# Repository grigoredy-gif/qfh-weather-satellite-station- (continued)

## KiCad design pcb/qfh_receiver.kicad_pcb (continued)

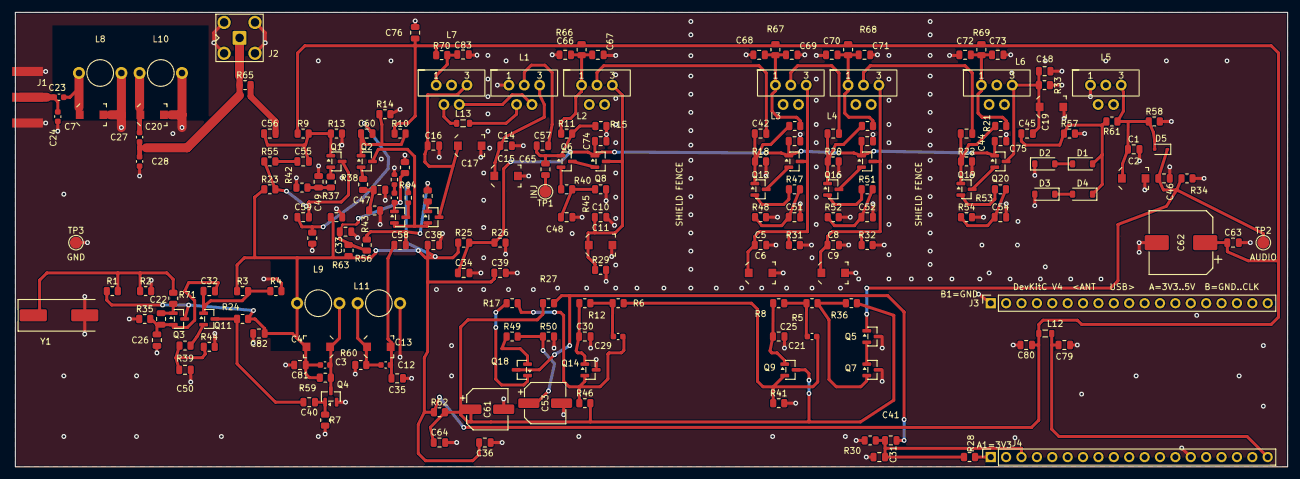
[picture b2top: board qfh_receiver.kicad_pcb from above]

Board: 2 copper layers, 210.0 x 75.0 mm, 205 parts (0 on the bottom side), 90 nets.

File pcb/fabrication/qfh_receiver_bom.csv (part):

"Refs","Value","Spec","Footprint","MPN","Farnell","Qty","DNP"
"C1,C5,C8,C10,C14,C16,C18,C35,C46","47p","NP0/C0G ceramic 0805, 50 V","Capacitor_SMD:C_0805_2012Metric","","","9",""
"C2,C6,C9,C11,C15,C17,C19","5.8-20p","SEHWA STC3MD20-T1 SMD trimmer 5.8-20 pF, N1300 (LCSC C22468122); pad 2 = rotor (cold side)","qfh_receiver:C_Trimmer_JZ_STC3","STC3MD20-T1","","7",""
"C3","4.7p","NP0/C0G 0603, 50 V, +/-0.25 pF (FH 0603CG4R7C500NT, LCSC C1669); fixed part of the x5 tank, with the 2-6 pF trimmer C4","Capacitor_SMD:C_0603_1608Metric","","","1",""
"C4","2-6p","SEHWA STC3MA06-T1 SMD trimmer 2-6 pF, Q 500 (LCSC C22468120); pad 2 = rotor (cold side, vcc)","qfh_receiver:C_Trimmer_JZ_STC3","STC3MA06-T1","","1",""
"C7,C13,C20","2-6p","SEHWA STC3MA06-T1 SMD trimmer 2-6 pF, Q 500 (LCSC C22468120); pad 2 = rotor (cold side)","qfh_receiver:C_Trimmer_JZ_STC3","STC3MA06-T1","","3",""
"C12","6.8p","NP0/C0G 0603, 50 V (FH 0603CG6R8C500NT, LCSC C1679); fixed part of the LO top arm, with the 2-6 pF trimmer C13","Capacitor_SMD:C_0603_1608Metric","","","1",""
"C21","2.7n","X7R 0603, 50 V, 10 % (FH 0603B272K500NT, LCSC C1609)","Capacitor_SMD:C_0603_1608Metric","","","1",""
"C22","22p","NP0/C0G 0805, 50 V; Colpitts C1 for a CL 20 pF crystal (22p in series with 180p + strays = about 20 pF)","Capacitor_SMD:C_0805_2012Metric","","","1",""
"C23,C27","10p","NP0/C0G 0603, 50 V, 5 % (Samsung CL10C100JB8NNNC, LCSC C1634); BPF tap, 10p/68p keeps the 0.128 ratio","Capacitor_SMD:C_0603_1608Metric","","","2",""
"C24,C28","68p","NP0/C0G 0603, 50 V, 5 % (Samsung CL10C680JB8NNNC, LCSC C28262); BPF tap","Capacitor_SMD:C_0603_1608Metric","","","2",""
"C25,C31","2.2n","C0G 0805, 50 V, 5 % (Samsung CL21C222JBFNNNE, LCSC C28260)","Capacitor_SMD:C_0805_2012Metric","","","2",""
"C26","180p","NP0/C0G ceramic 0805, 50 V","Capacitor_SMD:C_0805_2012Metric","","","1",""
"C29","8.2n","X7R 0603, 50 V, 10 % (FH 0603B822K500NT, LCSC C1322360)","Capacitor_SMD:C_0603_1608Metric","","","1",""
"C30","1n","X7R 0805, 50 V (Samsung CL21B102KBCNNNC, LCSC C46653); 1.2n -> 1.0n in the cost-down, audio corner 6.1 -> 6.6 kHz","Capacitor_SMD:C_0805_2012Metric","","","1",""
"C32,C33,C47","10n","X7R ceramic 0805, 50 V","Capacitor_SMD:C_0805_2012Metric","","","3",""
"C34,C36-C39,C48-C52,C54,C63,C64,C66-C82","100n","X7R ceramic 0805, 50 V","Capacitor_SMD:C_0805_2012Metric","","","30",""
"C40,C42-C45,C55-C60,C65","1n","X7R ceramic 0805, 50 V","Capacitor_SMD:C_0805_2012Metric","","","12",""
"C41","1u","X7R ceramic 0805, 16 V or more","Capacitor_SMD:C_0805_2012Metric","","","1",""
"C53,C61","100u","SMD aluminium electrolytic 16 V, 6.3x7.7 mm","Capacitor_SMD:CP_Elec_6.3x7.7","","","2",""
"C62","1000u","SMD aluminium electrolytic 1000 uF 10 V, 90 mOhm, D10 x 10.5 mm (JARSON FZ1A102M1010, LCSC C3646816)","Capacitor_SMD:CP_Elec_10x10","","","1",""
"C83","100n","X7R 0805, 50 V; L7 feed decoupling","Capacitor_SMD:C_0805_2012Metric","","","1",""
"C84","1n","X7R 0603, 50 V; Q15 base snubber with R74","Capacitor_SMD:C_0603_1608Metric","","","1",""
"D1-D4","1N4148W","SOD-123; same die as 1N4148","Diode_SMD:D_SOD-123","","","4",""
"D5","BAS70WS","Schottky 70 V, SOD-323, CT <= 2 pF (hongjiacheng BAS70WS, LCSC C7502716); slope-detector diode, replaces 1N5711WS (detector trimmer about +0.1 pF)","Diode_SMD:D_SOD-323","","","1",""
"J1","SMA antenna","Amphenol edge-launch SMA","Connector_Coaxial:SMA_Amphenol_132289_EdgeMount","132289","2112467","1",""
"J2","SMA test","BAT Wireless BWSMA-KWE-Z001 right-angle THT SMA (LCSC C496551), JLC THT assembly","Connector_Coaxial:SMA_BAT_Wireless_BWSMA-KWE-Z001","BWSMA-KWE-Z001","","1",""
"J3","ESP32 row B","female header 1x19, 2.54 mm, 8.5 mm stand-off (socket for ESP32-DevKitC V4 38-pin)","Connector_PinSocket_2.54mm:PinSocket_1x19_P2.54mm_Vertical","","","1",""
"J4","ESP32 row A","female header 1x19, 2.54 mm, 8.5 mm stand-off (socket for ESP32-DevKitC V4 38-pin)","Connector_PinSocket_2.54mm:PinSocket_1x19_P2.54mm_Vertical","","","1",""
"L1","2.2u tap13/27","T37-6 toroid: 27 t 0.4 mm enamelled, tap at turn 13, plus 2 t link winding on pads 4/5, wound at the cold end of the main winding (pad 1 side) (link loop in series with L13 680 nH; ground the loop with a wire from L1 pad 5 to L1 pad 1); return-wound (after the last turn lay the wire back once around the outside of the core to the start); mount on edge","qfh_receiver:TOROID_T37-6_UNIVERSAL","","","1",""
"L2-L4","2.2u tap13/27","T37-6 toroid: 27 t 0.4 mm enamelled, tap at turn 13; return-wound (after the last turn lay the wire back once around the outside of the core to the start); mount on edge","qfh_receiver:TOROID_T37-6_UNIVERSAL","","","3",""
"L5,L6","2.2u","T37-6 toroid: 27 t 0.4 mm enamelled; return-wound (after the last turn lay the wire back once around the outside of the core to the start); mount on edge","qfh_receiver:TOROID_T37-6_UNIVERSAL","","","2",""
"L7","2.2u","T37-6 toroid: 27 t 0.4 mm enamelled, plus 2 t link winding on pads 4/5, wound at the cold end of the main winding (pad 1 side) (link loop in series with L13 680 nH; ground the loop with a wire from L1 pad 5 to L1 pad 1); return-wound (after the last turn lay the wire back once around the outside of the core to the start); mount on edge","qfh_receiver:TOROID_T37-6_UNIVERSAL","","","1",""
"L8,L10","82n","air coil: 5 t 0.8 mm enamelled on a 5 mm former, one diameter from its pair; spread the turns evenly to about 7 mm long (Wheeler, +/-10 %: about 86 nH there, 82 nH at 7.5 mm; 7 mm centres the 2-6 pF trimmer better; wound tight it is about 120 nH)","qfh_receiver:AIRCOIL_5MM","","","2",""
"L9,L11","150n","air coil: 7 t 0.8 mm enamelled on a 5 mm former, one diameter from its pair; spread the turns evenly to about 8.2 mm long (Wheeler, +/-10 %: about 150 nH; wound tight it is about 190 nH)","qfh_receiver:AIRCOIL_5MM","","","2",""
"L12","FB 600R@100MHz","ferrite bead 0805, 600 ohm at 100 MHz, >= 200 mA","Inductor_SMD:L_0805_2012Metric","","","1",""
"L13","680n","0805 ceramic-core wirewound 680 nH 5 % (FH FHW0805UCR68JGT, LCSC C62554; Q 23 @ 50 MHz, SRF 300 MHz); in series with the 2 t L7/L1 link. Bench options: 560n FHW0805UCR56JGT (C139264), 820n FHW0805UCR82JGT (C139265)","Inductor_SMD:L_0805_2012Metric","","","1",""
"Q1-Q4,Q6,Q8,Q10-Q13,Q15-Q17,Q19,Q20","BFR92P","Infineon SOT-23 (min 5, multiples of 5 at Farnell)","Package_TO_SOT_SMD:SOT-23","BFR92PE6327HTSA1","","15",""
"Q5,Q7,Q14","MMBT3906","SOT-23 PNP MMBT3906 (hongjiacheng, marking 2A, LCSC C7420354), B-E-C pinout (pin 1 = B)","Package_TO_SOT_SMD:SOT-23","","","3",""
"Q9,Q18","MMBT3904","SOT-23, B-E-C pinout (pin 1 = B); same die as 2N3904","Package_TO_SOT_SMD:SOT-23","","","2",""
"R1","9.1k","thick film 0805, 1 %","Resistor_SMD:R_0805_2012Metric","","","1",""
"R2,R5,R7,R8,R26,R28,R29,R31-R33,R36,R46,R56","10k","thick film 0805, 1 %","Resistor_SMD:R_0805_2012Metric","","","13",""
"R3,R14,R15,R18,R20,R22","11k","thick film 0805, 1 %","Resistor_SMD:R_0805_2012Metric","","","6",""
"R4","5.1k","thick film 0805, 1 %","Resistor_SMD:R_0805_2012Metric","","","1",""
"R6,R12","7.5k","thick film 0805, 1 %","Resistor_SMD:R_0805_2012Metric","","","2",""
"R9,R50","820","thick film 0805, 1 %","Resistor_SMD:R_0805_2012Metric","","","2",""
"R10,R11,R16,R19,R21","27k","thick film 0805, 1 %","Resistor_SMD:R_0805_2012Metric","","","5",""
"R13,R35","560","thick film 0805, 1 %","Resistor_SMD:R_0805_2012Metric","","","2",""
"R17","1k","thick film 0805, 1 %","Resistor_SMD:R_0805_2012Metric","","","1",""
"R23","120","thick film 0805, 1 %","Resistor_SMD:R_0805_2012Metric","","","1",""
"R24,R45,R48,R52,R54","330","thick film 0805, 1 %","Resistor_SMD:R_0805_2012Metric","","","5",""
"R25,R60","6.8k","thick film 0805, 1 %","Resistor_SMD:R_0805_2012Metric","","","2",""
"R27","3.3k","thick film 0805, 1 %","Resistor_SMD:R_0805_2012Metric","","","1",""
"R30","6.2k","thick film 0805, 1 %","Resistor_SMD:R_0805_2012Metric","","","1",""
"R34","220k","thick film 0805, 1 %","Resistor_SMD:R_0805_2012Metric","","","1",""
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
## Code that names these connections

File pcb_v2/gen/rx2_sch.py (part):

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             {1: "ant", 2: "0"}, {"LCSC": "C496549", "MPN": "BWSMA-KE-Z001", "Assembly": "by hand"})]),
    "reg": ("ESP32 DevKitC, 38 pins (not in the simulation)",
            ["Two 1x19 sockets, 2.54 mm, soldered by hand (LCSC C2932678); the DevKitC plugs in. Rows 25.4 mm apart, as on version 1.",
             "Pins used (Espressif's pin table of the DevKitC V4): left row J2 pin 1 = 3V3 (v3ref), pin 3 = GPIO36 / VP (adc), pin 14 = GND,",
             "pin 19 = 5V (v5); right row J3 pins 1 and 7 = GND. Pin 1 is at the antenna end of the module. All other pins stay free."],
            [("devkitc_left", "Connector:Conn_01x19_Socket", "DevKitC_left", SOCKET,
              {1: "v3ref", 3: "adc", 14: "0", 19: "v5"},
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ROOT_TEXT = [
    (2.2, "QFH 137 MHz weather-satellite receiver, version 2: all discrete, assembled by JLCPCB"),
    (1.5, "Signal: antenna 137.9 MHz -> 1 front end -> 4 mixer 1 (LO 125 MHz from 2 and 3) -> 5 first IF 12.9 MHz"),
    (1.5, "-> 7 mixer 2 (LO 14.318 MHz from 6) -> 8 second IF 1.418 MHz, limiter, detector -> 9 audio -> ESP32 DevKitC, GPIO36."),
    (1.5, "Power: 10 regulator (rail VCC, 3.3 V: copies the DevKitC's 3V3 pin, fed from its 5V pin), 11 the bias references vb and vbd."),
    (1.5, ""),
    (1.5, "This schematic is generated by pcb_v2/gen/rx2_sch.py from the simulation blocks fm_receiver_v2/simulations/rx2_blk_*.inc."),
    (1.5, "Net names are the node names of the simulation. Under each value stands the part's name in the simulation (field Sim)."),
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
